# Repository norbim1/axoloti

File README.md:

Axoloti
=======
Axoloti is a platform for sketching music-DSP algorithms running on standalone hardware.
www.axoloti.be

by Johannes Taelman
johannes.taelman@gmail.com

Launching Axoloti
requires Java runtime.
* on OSX: doubleclick Axoloti.command
* on Windows: doubleclick Axoloti.bat
* on Linux: doubleclick Axoloti.sh

documentation: in the folder doc/

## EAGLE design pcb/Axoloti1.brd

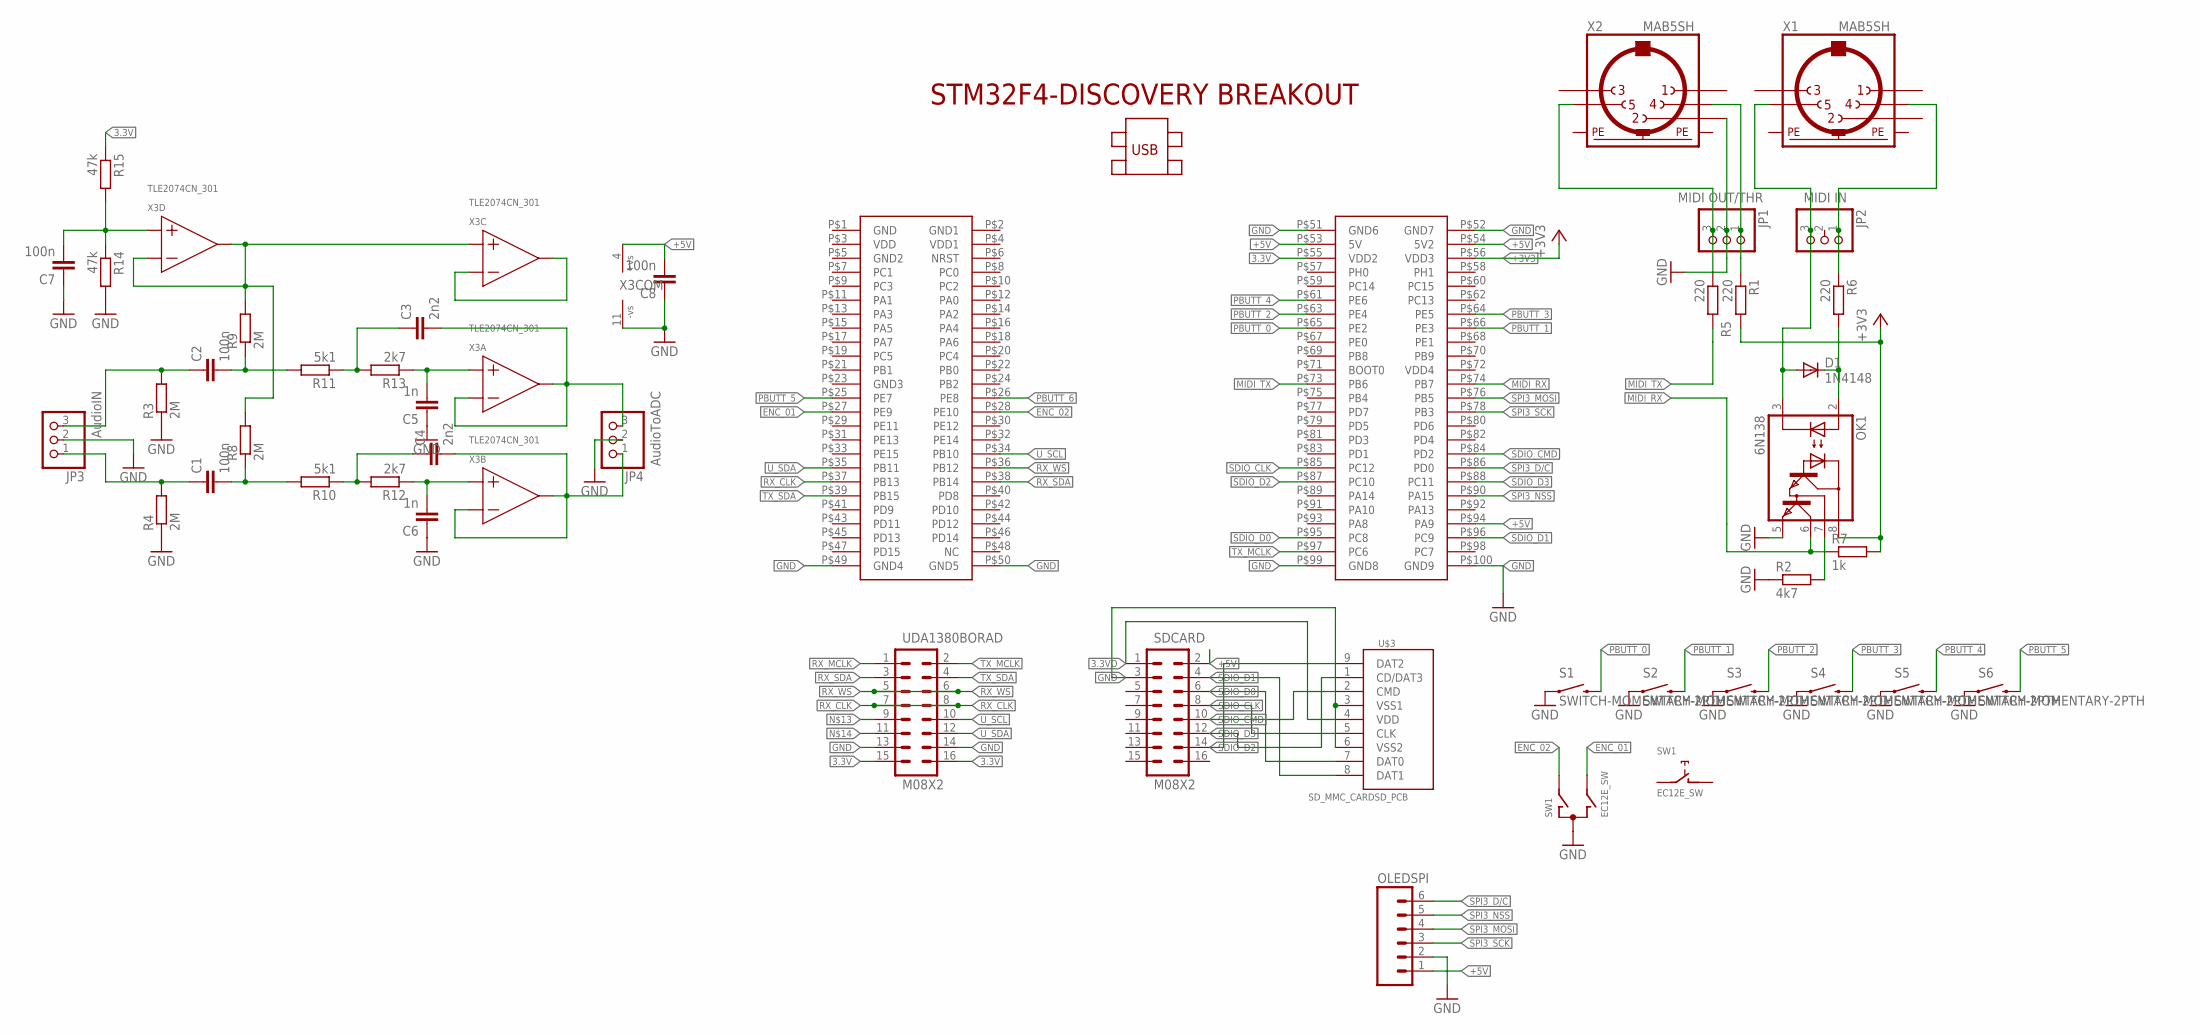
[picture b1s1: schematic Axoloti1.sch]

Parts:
C1, C2, C7, C8: 100n; C025-025X050
C3, C4: 2n2; C025-025X050
C5, C6: 1n; C025-025X050
D1: 1N4148; DO35-7
JP1: MIDI OUT/THR; 1X03
JP2: MIDI IN; 1X03
JP3: AudioIN; 1X03
JP4: AudioToADC; 1X03
OK1: 6N138; DIL08
OLEDSPI: M06SIP; 1X06
R1, R5, R6: 220; 0204/7
R2: 4k7; 0204/7
R3, R4, R8, R9: 2M; 0204/7
R7: 1k; 0204/7
R10, R11: 5k1; 0204/7
R12, R13: 2k7; 0204/7
R14, R15: 47k; 0204/7
S1, S2, S3, S4, S5, S6: SWITCH-MOMENTARY-2PTH; TACTILE-PTH
SDCARD: M08X2; 2X8
SW1: EC12E_SW; ALPS_EC12E_SW
U$1: STM32F4-DISCOVERY
U$3: SD_MMC_CARDSD_PCB; SD-MMC-CARD
UDA1380BORAD: M08X2; 2X8
X1, X2: MAB5SH
X3: TLE2074CN_301; DIL14

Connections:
3.3V: R15.1, U$1.P$55 (VDD2), UDA1380BORAD.15, UDA1380BORAD.16
3.3VO: SDCARD.1, U$3.4 (VDD)
+3V3: OK1.8 (VCC), R1.2, R7.2, U$1.P$56 (VDD3)
+5V: C8.2, OLEDSPI.1, SDCARD.2, U$1.P$53 (5V), U$1.P$54 (5V2), U$1.P$94 (PA9), X3.4 (+VS)
ENC_01: SW1.B, U$1.P$27 (PE9)
ENC_02: SW1.A, U$1.P$28 (PE10)
GND: C5.1, C6.1, C7.1, C8.1, JP1.2, JP3.2, JP4.2, OK1.5 (GND), OLEDSPI.2, R2.1, R3.1, R4.1, R14.2, S1.1, S2.1, S3.1, S4.1, S5.1, S6.1, SDCARD.3, SW1.C, U$1.P$49 (GND4), U$1.P$50 (GND5), U$1.P$51 (GND6), U$1.P$52 (GND7), U$1.P$99 (GND8), U$1.P$100 (GND9), U$3.3 (VSS1), U$3.6 (VSS2), UDA1380BORAD.13, UDA1380BORAD.14, X2.2, X3.11 (-VS)
MIDI_RX: OK1.6 (VO), R7.1, U$1.P$74 (PB7)
MIDI_TX: R5.2, U$1.P$73 (PB6)
unnamed: JP1.3, R5.1, X2.5
unnamed: C4.2, JP4.1, X3.6 (-IN), X3.7 (OUT)
unnamed: OK1.7 (VB), R2.2
unnamed: C3.2, JP4.3, X3.1 (OUT), X3.2 (-IN)
unnamed: C5.2, R13.1, X3.3 (+IN)
unnamed: C3.1, R11.1, R13.2
unnamed: C4.1, R10.1, R12.2
unnamed: C6.2, R12.1, X3.5 (+IN)
unnamed: C2.2, R9.1, R11.2
unnamed: C1.2, R8.1, R10.2
unnamed: C1.1, JP3.1, R4.2
unnamed: C2.1, JP3.3, R3.2
unnamed: JP1.1, R1.1, X2.4
unnamed: D1.A, JP2.3, OK1.3 (C), X1.5
unnamed: D1.C, OK1.2 (A), R6.2
unnamed: JP2.1, R6.1, X1.4
unnamed: R8.2, R9.2, X3.10 (+IN), X3.13 (-IN), X3.14 (OUT)
unnamed: C7.2, R14.1, R15.2, X3.12 (+IN)
unnamed: X3.8 (OUT), X3.9 (-IN)
PBUTT_0: S1.3 (2), U$1.P$65 (PE2)
PBUTT_1: S2.3 (2), U$1.P$66 (PE3)
PBUTT_2: S3.3 (2), U$1.P$63 (PE4)
PBUTT_3: S4.3 (2), U$1.P$64 (PE5)
PBUTT_4: S5.3 (2), U$1.P$61 (PE6)
PBUTT_5: S6.3 (2), U$1.P$25 (PE7)
PBUTT_6: U$1.P$26 (PE8)
PE: X1.PE, X1.PE@ (PE), X2.PE, X2.PE@ (PE)
RX_CLK: U$1.P$37 (PB13), UDA1380BORAD.7, UDA1380BORAD.8
RX_MCLK: UDA1380BORAD.1
RX_SDA: U$1.P$38 (PB14), UDA1380BORAD.3
RX_WS: U$1.P$36 (PB12), UDA1380BORAD.5, UDA1380BORAD.6
SDIO_CLK: SDCARD.8, U$1.P$85 (PC12), U$3.5 (CLK)
SDIO_CMD: SDCARD.10, U$1.P$84 (PD2), U$3.2 (CMD)
SDIO_D0: SDCARD.6, U$1.P$95 (PC8), U$3.7 (DAT0)
SDIO_D1: SDCARD.4, U$1.P$96 (PC9), U$3.8 (DAT1)
SDIO_D2: SDCARD.14, U$1.P$87 (PC10), U$3.9 (DAT2)
SDIO_D3: SDCARD.12, U$1.P$88 (PC11), U$3.1 (CD/DAT3)
SPI3_D/C: OLEDSPI.6, U$1.P$86 (PD0)
SPI3_MOSI: OLEDSPI.4, U$1.P$76 (PB5)
SPI3_NSS: OLEDSPI.5, U$1.P$90 (PA15)
SPI3_SCK: OLEDSPI.3, U$1.P$78 (PB3)
TX_MCLK: U$1.P$97 (PC6), UDA1380BORAD.2
TX_SDA: U$1.P$39 (PB15), UDA1380BORAD.4
U_SCL: U$1.P$34 (PB10), UDA1380BORAD.10
U_SDA: U$1.P$35 (PB11), UDA1380BORAD.12

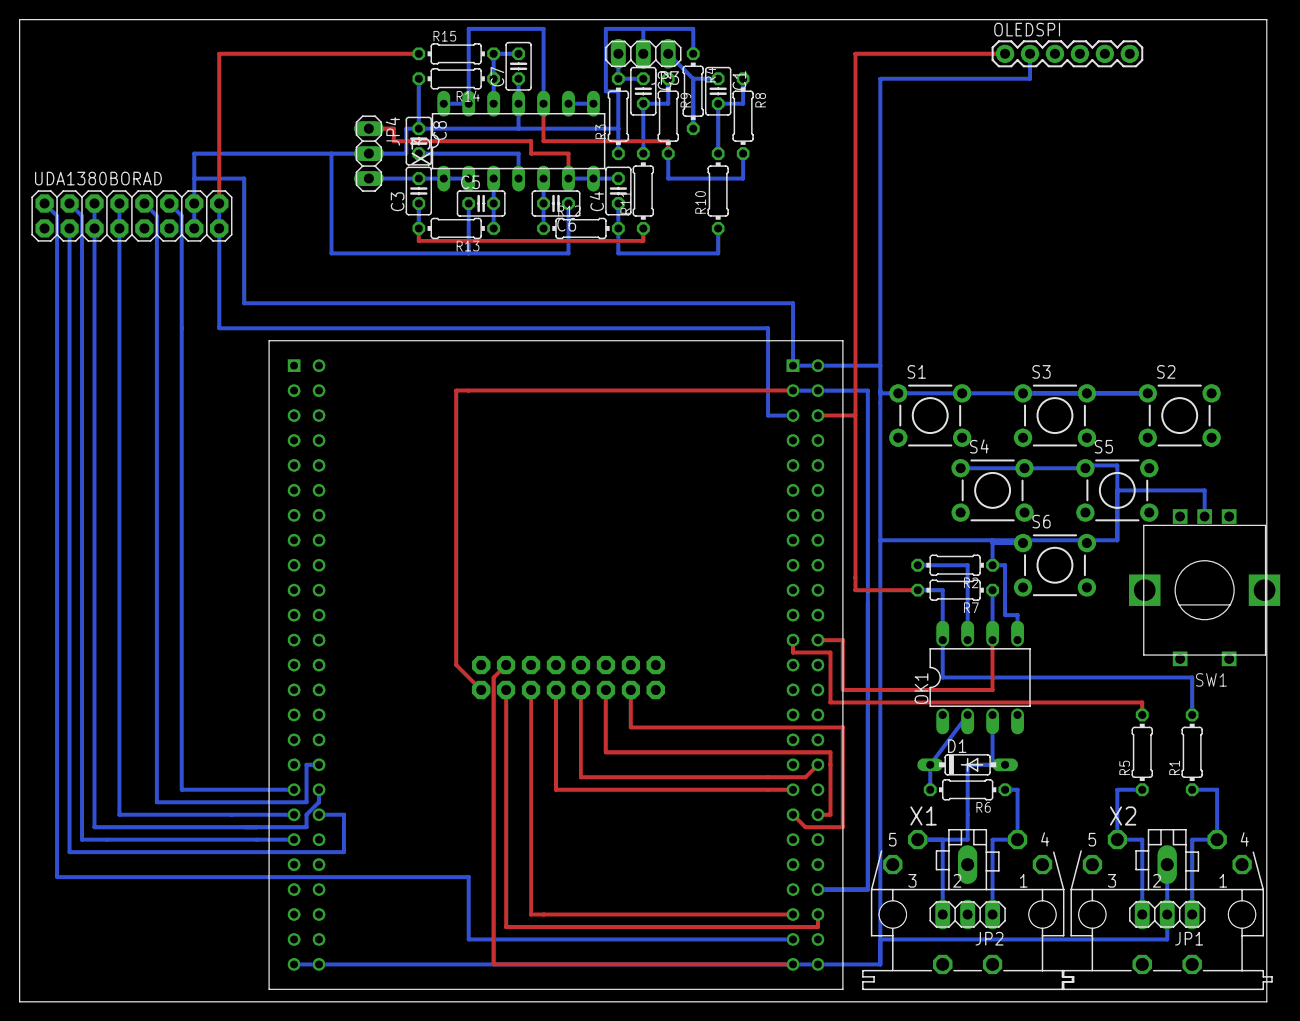
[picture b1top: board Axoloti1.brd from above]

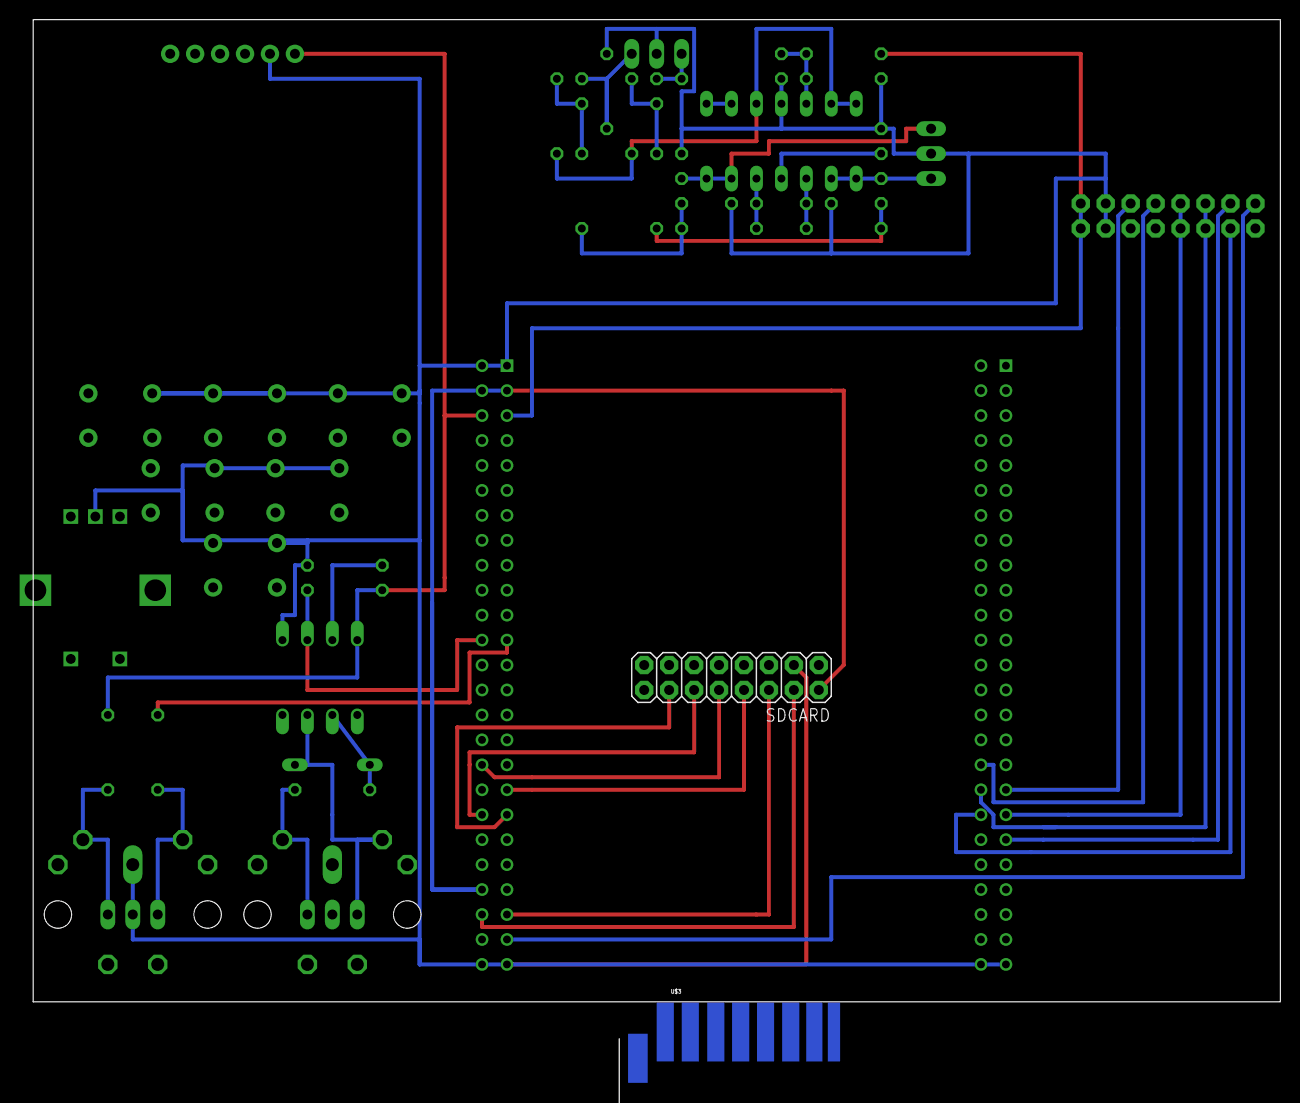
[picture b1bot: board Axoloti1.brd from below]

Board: 4 copper layers, 127.0 x 100.0 mm, 44 parts (2 on the bottom side), 52 nets.

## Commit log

2015-01-26 fixup
2015-01-26 demo readme
2015-04-26 F4Discovery + UDA1380 audio board
2015-05-03 Local control surface
2015-11-08 Encoder pin change
2016-05-12 merged
2016-08-31 UI refinement

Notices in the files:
parts and their libraries:
SparkFun: Licensing: CC v3.0 Share-Alike You are welcome to use this library for commercial purposes.
